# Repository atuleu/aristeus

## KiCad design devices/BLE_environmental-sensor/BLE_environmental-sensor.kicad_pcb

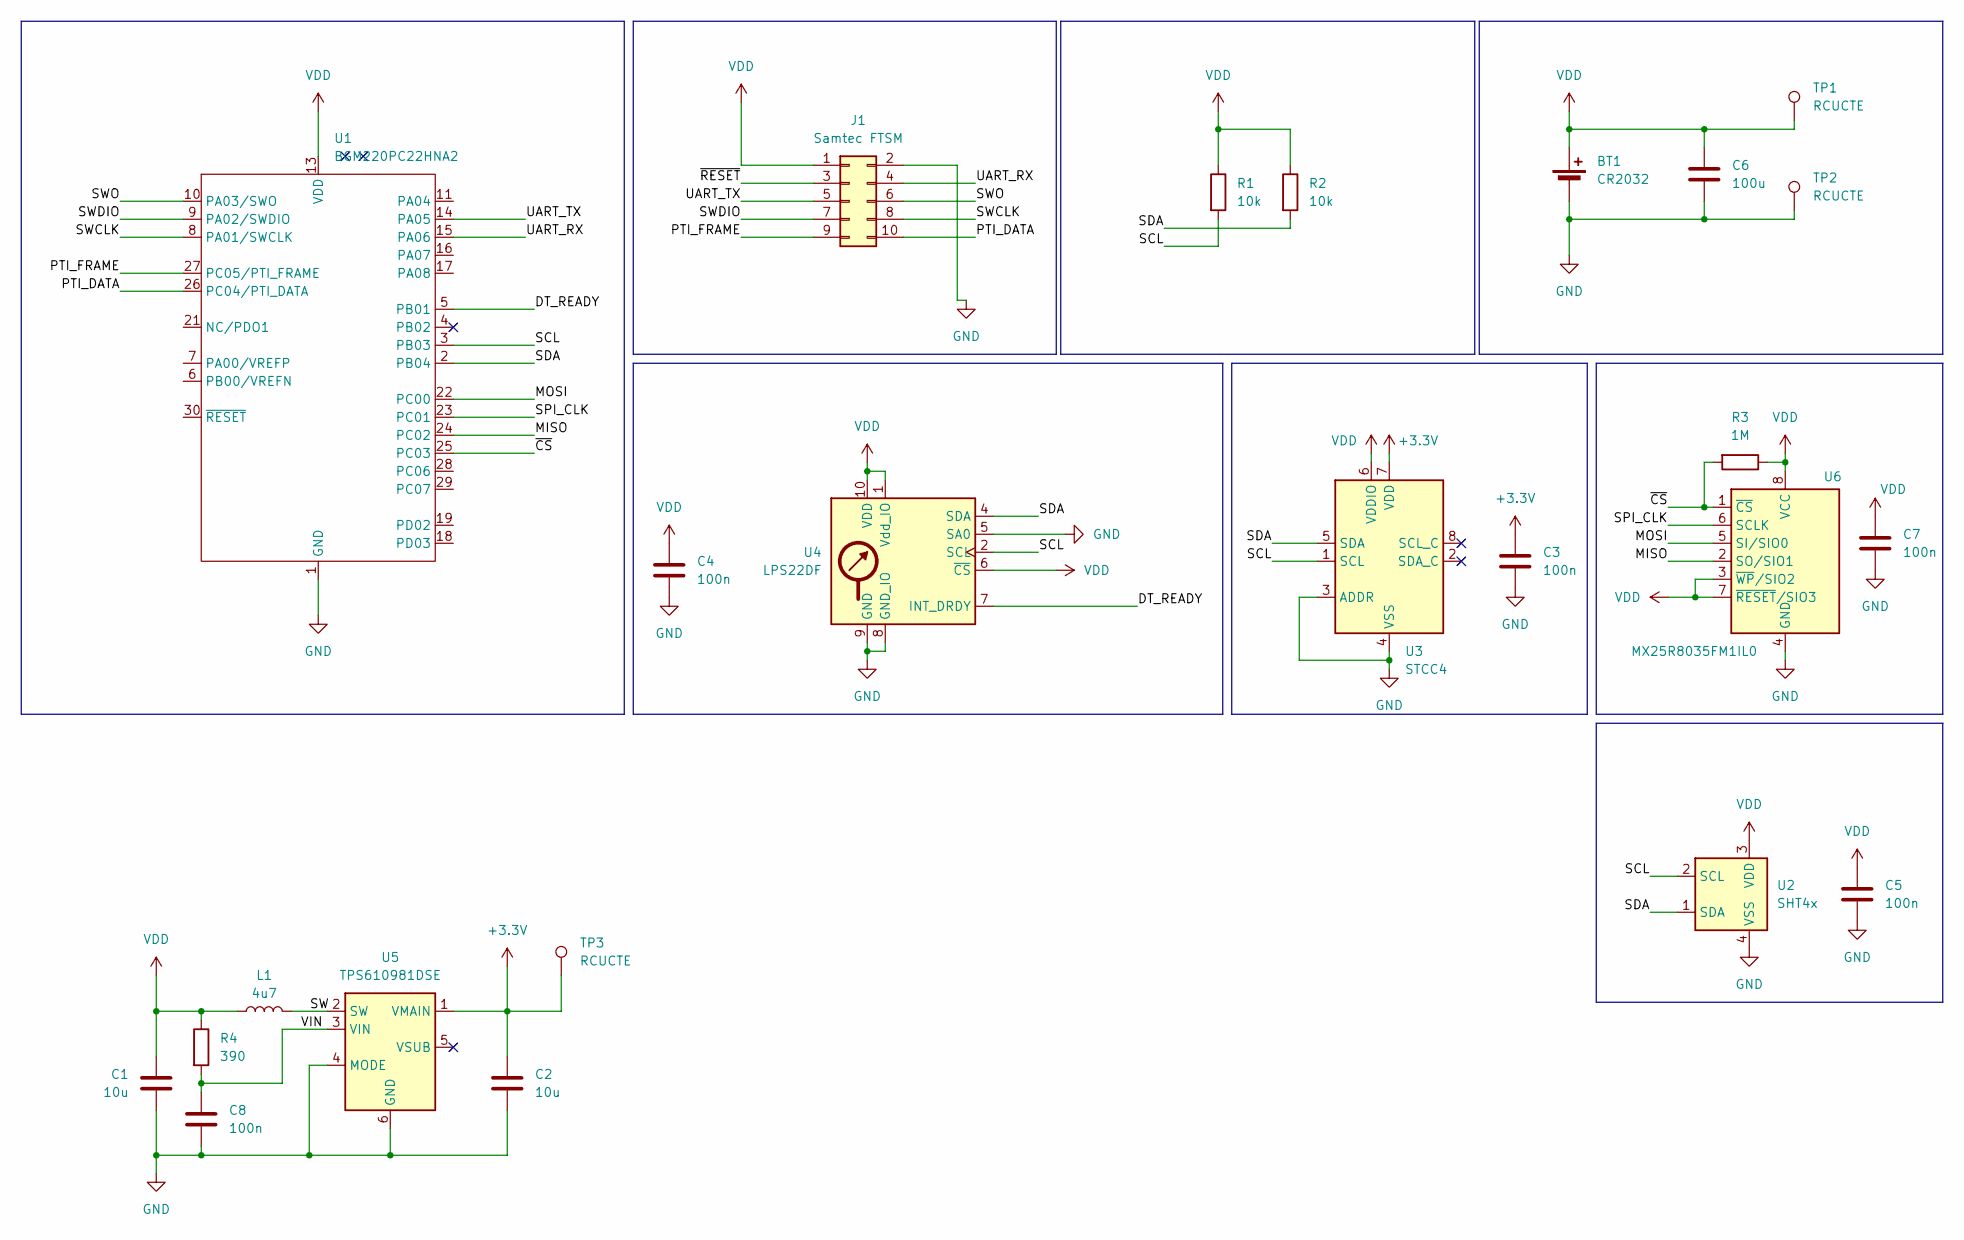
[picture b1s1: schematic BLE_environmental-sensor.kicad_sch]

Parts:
BT1: CR2032; BatteryHolder_TE_BAT-HLD-001; MPN BAT-HLD-001
C1, C2: 10u; C_0805_2012Metric; MPN GRM219R61A106KE44D
C3, C4, C5, C7, C8: 100n; C_0603_1608Metric; MPN CL10B104KB8NNNC
C6: 100u; C_1206_3216Metric; MPN CL31A107MQHNNWE
J1: Samtec FTSM; Tag-Connect_TC2050-IDC-NL_2x05_P1.27mm_Vertical; MPN TC2050-IDC-NL
L1: 4u7; L_Bourns-SRN3015; MPN SRN3015TA-4R7M
R1, R2: 10k; R_0603_1608Metric; MPN RC0603FR-0710KL
R3: 1M; R_0603_1608Metric; MPN RC0603FR-071ML
R4: 390; R_0603_1608Metric; MPN RC0603FR-07390RL
TP1, TP2, TP3: RCUCTE; MPN RCUCTE
U1: BGM220PC22HNA2; SiliconLab_BGM220P; MPN BGM220PC22HNA2
U2: SHT4x; Sensirion_DFN-4_1.5x1.5mm_P0.8mm_SHT4x_NoCentralPad; MPN SHT41-AD1F-R2
U3: STCC4; Sensirion_STCC4_4x3_P1.15mm; MPN STCC4
U4: LPS22DF; ST_HLGA-10_2x2mm_P0.5mm_LayoutBorder3x2y; MPN LPS22DFTR
U5: TPS610981DSE; WSON-6_1.5x1.5mm_P0.5mm; MPN TPS610981DSE
U6: MX25R8035FM1IL0; JEITA_SOIC-8_3.9x4.9mm_P1.27mm; MPN MX25R8035FM1IL0

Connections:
+3.3V: C2.1, C3.1, TP3.1 (1_1), U3.7 (VDD), U5.1 (VMAIN)
/DT_READY: U1.5 (PB01), U4.7 (INT_DRDY)
/MISO: U1.24 (PC02), U6.2 (SO/SIO1)
/MOSI: U1.22 (PC00), U6.5 (SI/SIO0)
/PTI_DATA: J1.10, U1.26 (PC04/PTI_DATA)
/PTI_FRAME: J1.9, U1.27 (PC05/PTI_FRAME)
/SCL: R1.2, U1.3 (PB03), U2.2 (SCL), U3.1 (SCL), U4.2 (SCL)
/SDA: R2.2, U1.2 (PB04), U2.1 (SDA), U3.5 (SDA), U4.4 (SDA)
/SPI_CLK: U1.23 (PC01), U6.6 (SCLK)
/SW: L1.2, U5.2 (SW)
/SWCLK: J1.8, U1.8 (PA01/SWCLK)
/SWDIO: J1.7, U1.9 (PA02/SWDIO)
/SWO: J1.6, U1.10 (PA03/SWO)
/UART_RX: J1.4, U1.15 (PA06)
/UART_TX: J1.5, U1.14 (PA05)
/VIN: C8.1, R4.2, U5.3 (VIN)
/~CS: R3.2, U1.25 (PC03), U6.1 (~CS)
/~RESET: J1.3
GND: BT1.2 (-), C1.2, C2.2, C3.2, C4.2, C5.2, C6.2, C7.2, C8.2, J1.2, TP2.1 (1_1), U1.1 (GND), U1.12 (GND), U1.20 (GND), U1.31 (GND), U2.4 (VSS), U3.3 (ADDR), U3.4 (VSS), U4.3 (GND), U4.5 (SA0), U4.8 (GND_IO), U4.9 (GND), U5.4 (MODE), U5.6 (GND), U6.4 (GND)
VDD: BT1.1 (+), C1.1, C4.1, C5.1, C6.1, C7.1, J1.1, L1.1, R1.1, R2.1, R3.1, R4.1, TP1.1 (1_1), U1.13 (VDD), U2.3 (VDD), U3.6 (VDDIO), U4.1 (Vdd_IO), U4.6 (~CS), U4.10 (VDD), U6.3 (~WP/SIO2), U6.7 (~RESET/SIO3), U6.8 (VCC)

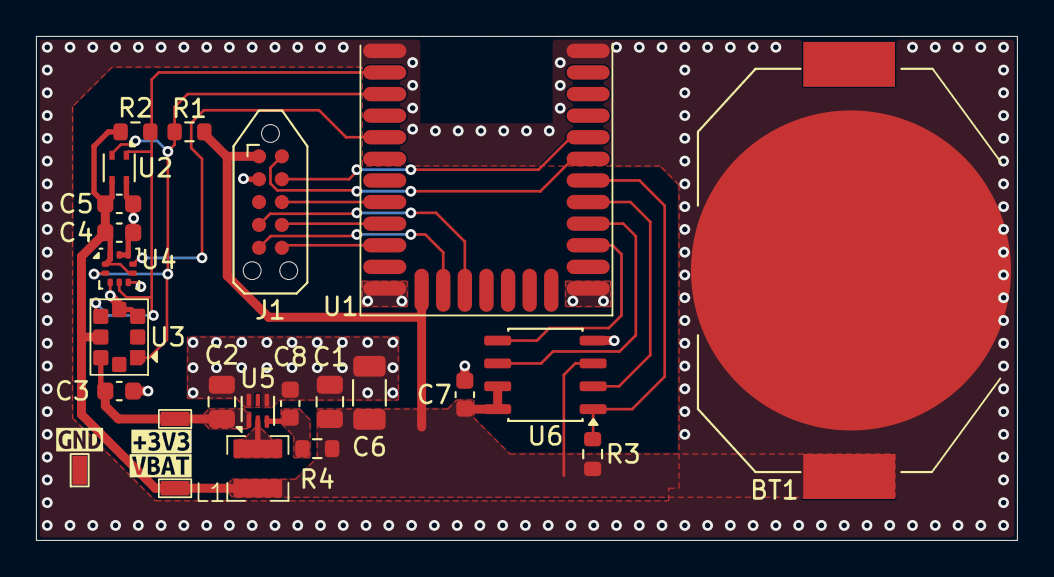
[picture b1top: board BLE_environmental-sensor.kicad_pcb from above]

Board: 2 copper layers, 54.5 x 28.0 mm, 29 parts (2 on the bottom side), 19 nets.

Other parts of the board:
kibuzzard-6A3D4B4B: G***; kibuzzard-6A3D4B4B
kibuzzard-6A3D4B8C: G***; kibuzzard-6A3D4B8C
kibuzzard-6A3D4B61: G***; kibuzzard-6A3D4B61
kibuzzard-6A3D4E4D: G***; kibuzzard-6A3D4E4D
kibuzzard-6A7308BE: G***; kibuzzard-6A7308BE

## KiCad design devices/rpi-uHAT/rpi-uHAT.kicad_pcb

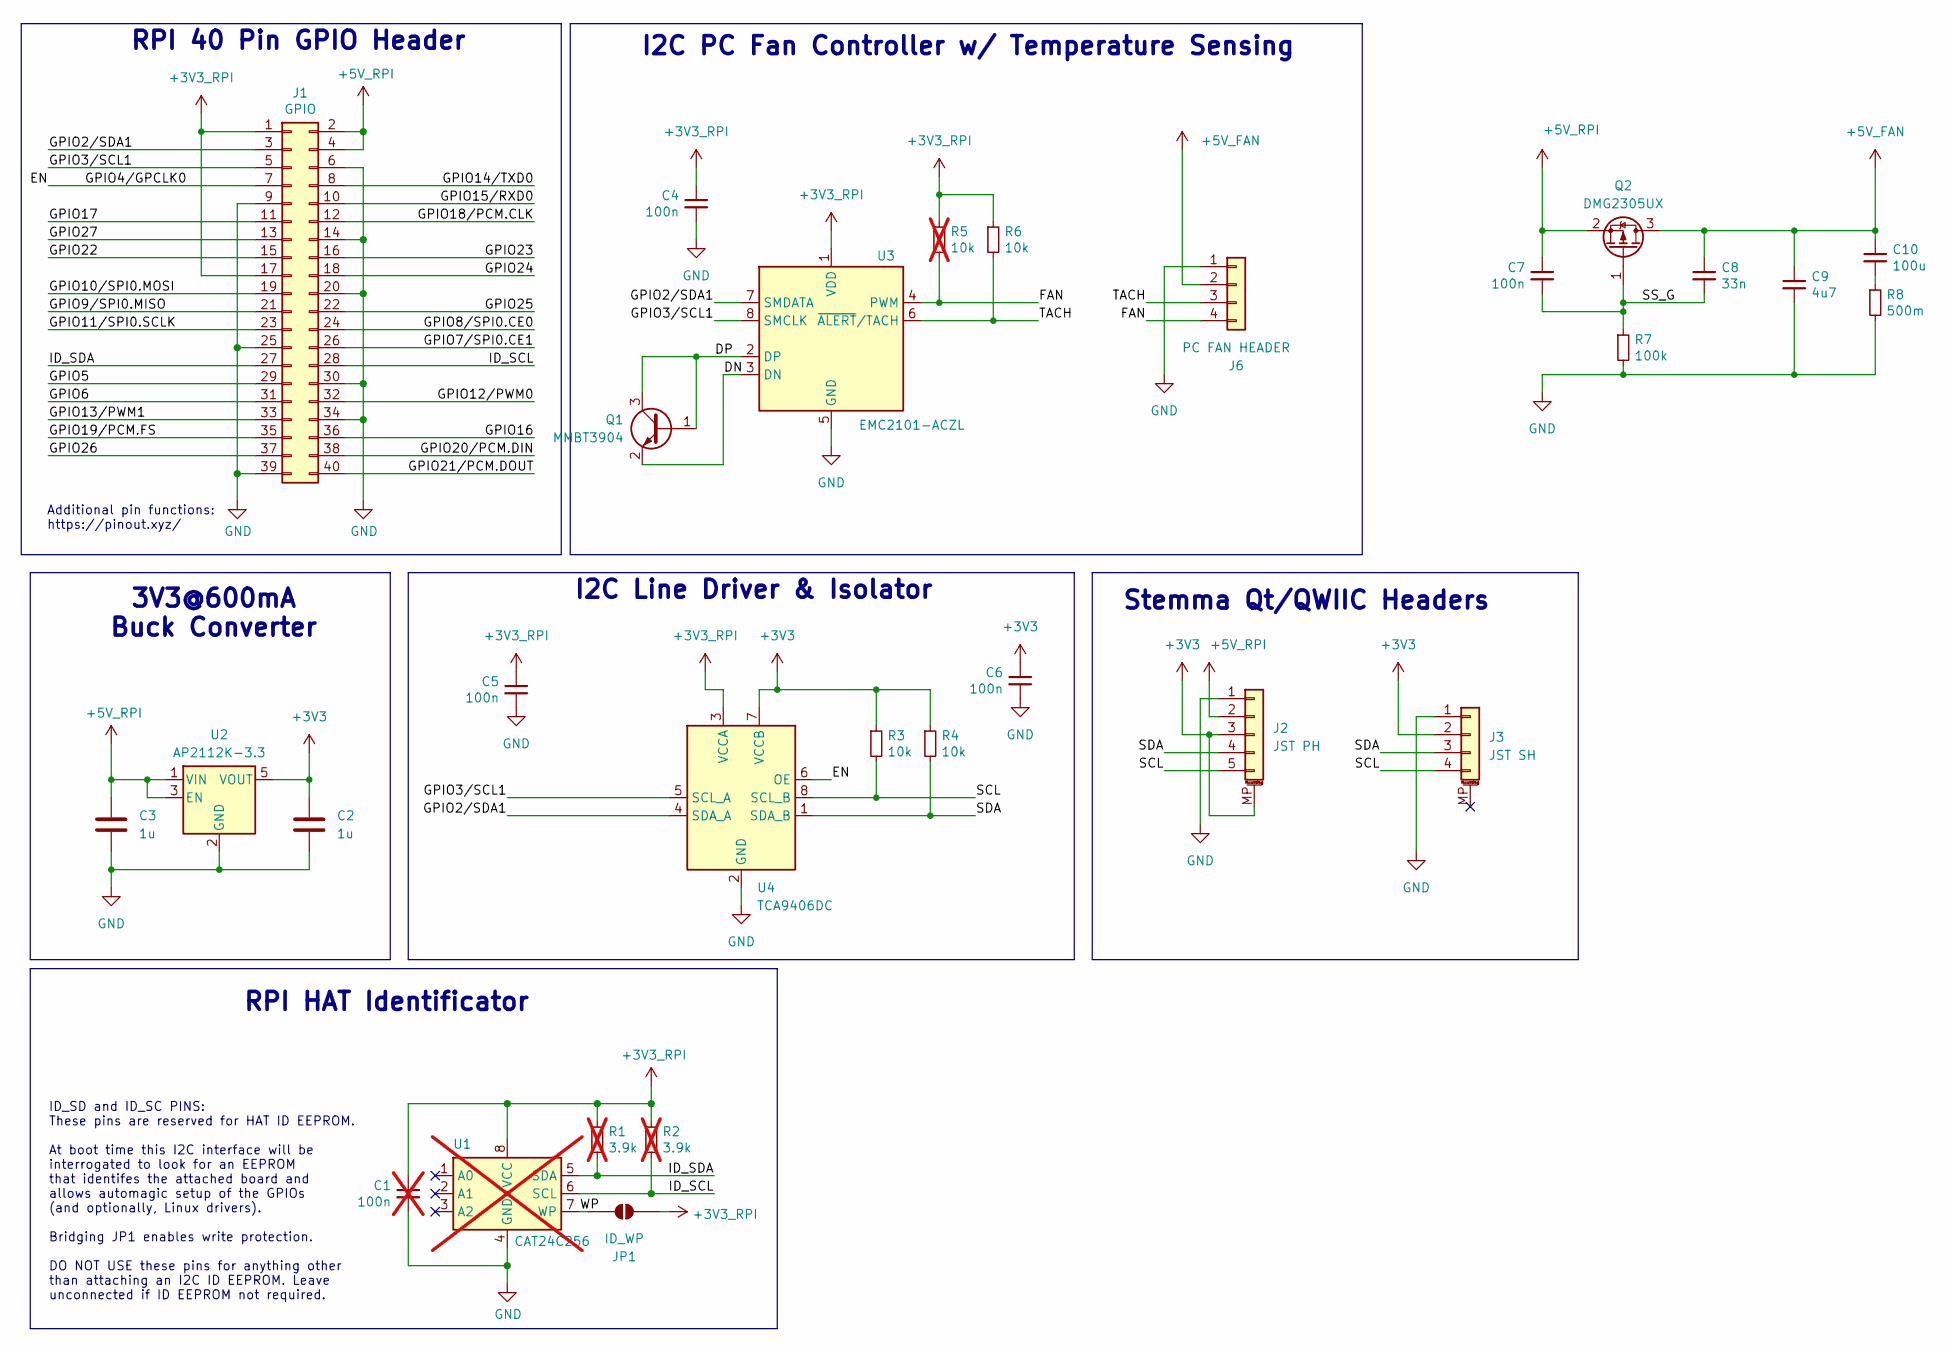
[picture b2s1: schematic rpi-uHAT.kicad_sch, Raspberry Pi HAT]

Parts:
C1: 100n; C_0603_1608Metric; MPN CL10B104KB8NNWC; not fitted
C2, C3: 1u; C_0805_2012Metric; MPN CL21B105KAFNNNE
C4, C5, C6, C7: 100n; C_0603_1608Metric; MPN CL10B104KB8NNWC
C8: 33n; C_0603_1608Metric; MPN CL10B104KB8NNWC
C9: 4u7; C_0805_2012Metric; MPN CL10B104KB8NNWC
C10: 100u; C_1206_3216Metric; MPN CL10B104KB8NNWC
J1: GPIO; PinSocket_2x20_P2.54mm_Vertical; MPN HLE-120-02-F-DV-BE
J2: JST PH; JST_PH_B5B-PH-SM4-TB_1x05-1MP_P2.00mm_Vertical; MPN B5B-PH-SM4-TB
J3: JST SH; JST_SH_BM04B-SRSS-TB_1x04-1MP_P1.00mm_Vertical; MPN BM04B-SRSS-TB
J6: PC FAN HEADER; FanPinHeader_1x04_P2.54mm_Vertical; MPN 47053-1000
JP1: ID_WP; SolderJumper-2_P1.3mm_Open_RoundedPad1.0x1.5mm
Q1: MMBT3904; SOT-23; MPN MMBT3904
Q2: DMG2305UX; SOT-23; MPN DMG2305UX
R1, R2: 3.9k; R_0603_1608Metric; MPN RC0603FR-073K9L; not fitted
R3, R4, R6: 10k; R_0603_1608Metric; MPN RC0603FR-0710KL
R5: 10k; R_0603_1608Metric; MPN RC0603FR-0710KL; not fitted
R7: 100k; R_0603_1608Metric; MPN RC0603FR-0710KL
R8: 500m; R_0603_1608Metric; MPN RC0603FR-0710KL
U1: CAT24C256; SOIC-8_3.9x4.9mm_P1.27mm; MPN CAT24C256; not fitted
U2: AP2112K-3.3; SOT-23-5; MPN AP2112K-3.3
U3: EMC2101-ACZL; MSOP-8_3x3mm_P0.65mm; MPN EMC2101-ACZL-TR
U4: TCA9406DC; TSSOP-8_3x3mm_P0.65mm; MPN TCA9406DC

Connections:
+3V3: C2.1, C6.1, J2.3, J2.MP (MountPin), J3.2, R3.1, R4.1, U2.5 (VOUT), U4.7 (VCCB)
+3V3_RPI: C1.1, C4.1, C5.1, J1.1, J1.17, JP1.2 (B), R1.1, R2.1, R5.1, R6.1, U1.8 (VCC), U3.1 (VDD), U4.3 (VCCA)
+5V_FAN: C8.1, C9.1, C10.1, J6.2, Q2.3 (D)
+5V_RPI: C3.1, C7.1, J1.2, J1.4, J2.2, Q2.2 (S), U2.1 (VIN), U2.3 (EN)
/DN: Q1.2 (E), U3.3 (DN)
/DP: Q1.1 (B), Q1.3 (C), U3.2 (DP)
/EN: J1.7, U4.6 (OE)
/FAN: J6.4, R5.2, U3.4 (PWM)
/GPIO2/SDA1: J1.3, U3.7 (SMDATA), U4.4 (SDA_A)
/GPIO3/SCL1: J1.5, U3.8 (SMCLK), U4.5 (SCL_A)
/GPIO5: J1.29
/GPIO6: J1.31
/GPIO7/SPI0.CE1: J1.26
/GPIO8/SPI0.CE0: J1.24
/GPIO9/SPI0.MISO: J1.21
/GPIO10/SPI0.MOSI: J1.19
/GPIO11/SPI0.SCLK: J1.23
/GPIO12/PWM0: J1.32
/GPIO13/PWM1: J1.33
/GPIO14/TXD0: J1.8
/GPIO15/RXD0: J1.10
/GPIO16: J1.36
/GPIO17: J1.11
/GPIO18/PCM.CLK: J1.12
/GPIO19/PCM.FS: J1.35
/GPIO20/PCM.DIN: J1.38
/GPIO21/PCM.DOUT: J1.40
/GPIO22: J1.15
/GPIO23: J1.16
/GPIO24: J1.18
/GPIO25: J1.22
/GPIO26: J1.37
/GPIO27: J1.13
/ID_SCL: J1.28, R2.2, U1.6 (SCL)
/ID_SDA: J1.27, R1.2, U1.5 (SDA)
/SCL: J2.5, J3.4, R3.2, U4.8 (SCL_B)
/SDA: J2.4, J3.3, R4.2, U4.1 (SDA_B)
/SS_G: C7.2, C8.2, Q2.1 (G), R7.1
/TACH: J6.3, R6.2, U3.6 (~ALERT/TACH)
/WP: JP1.1 (A), U1.7 (WP)
GND: C1.2, C2.2, C3.2, C4.2, C5.2, C6.2, C9.2, J1.6, J1.9, J1.14, J1.20, J1.25, J1.30, J1.34, J1.39, J2.1, J3.1, J6.1, R7.2, R8.2, U1.4 (GND), U2.2 (GND), U3.5 (GND), U4.2 (GND)
unnamed: C10.2, R8.1

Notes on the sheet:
3V3@600mA Buck Converter
I2C Line Driver & Isolator
ID_SD and ID_SC PINS: These pins are reserved for HAT ID EEPROM. At boot time this I2C interface will be interrogated to look for an EEPROM that identifes the attached board and allows automagic setup of the GPIOs (and optionally, Linux drivers). Bridging JP1 enables write protection. DO NOT USE th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
RPI 40 Pin GPIO Header
Stemma Qt/QWIIC Headers
I2C PC Fan Controller w/ Temperature Sensing
RPI HAT Identificator
Additional pin functions: https://pinout.xyz/

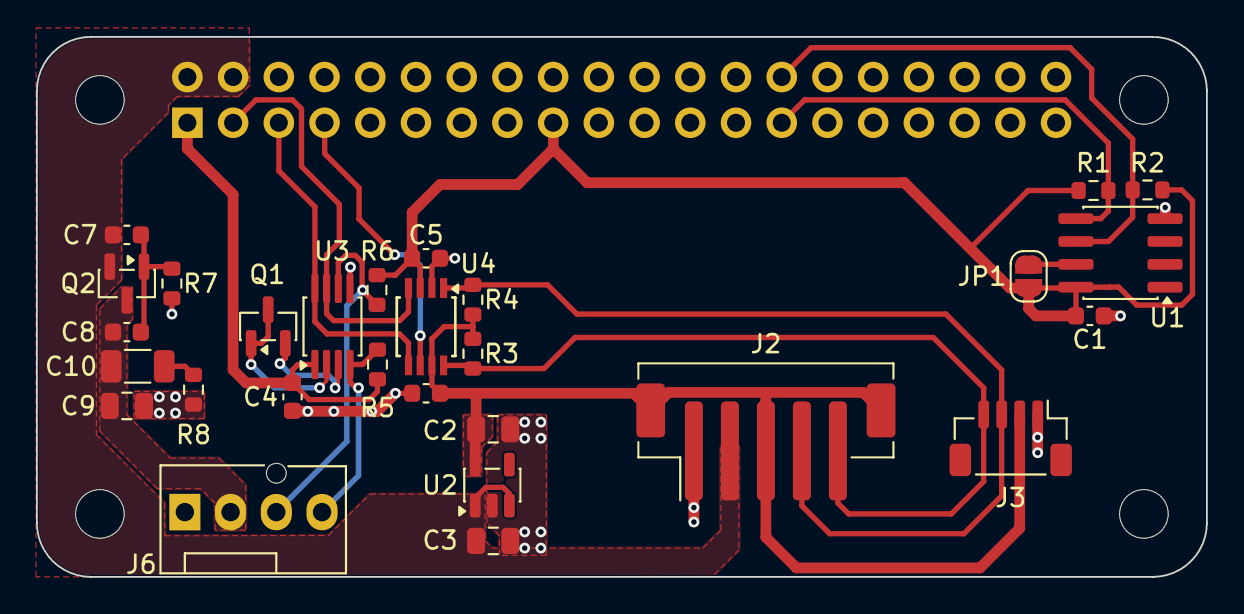
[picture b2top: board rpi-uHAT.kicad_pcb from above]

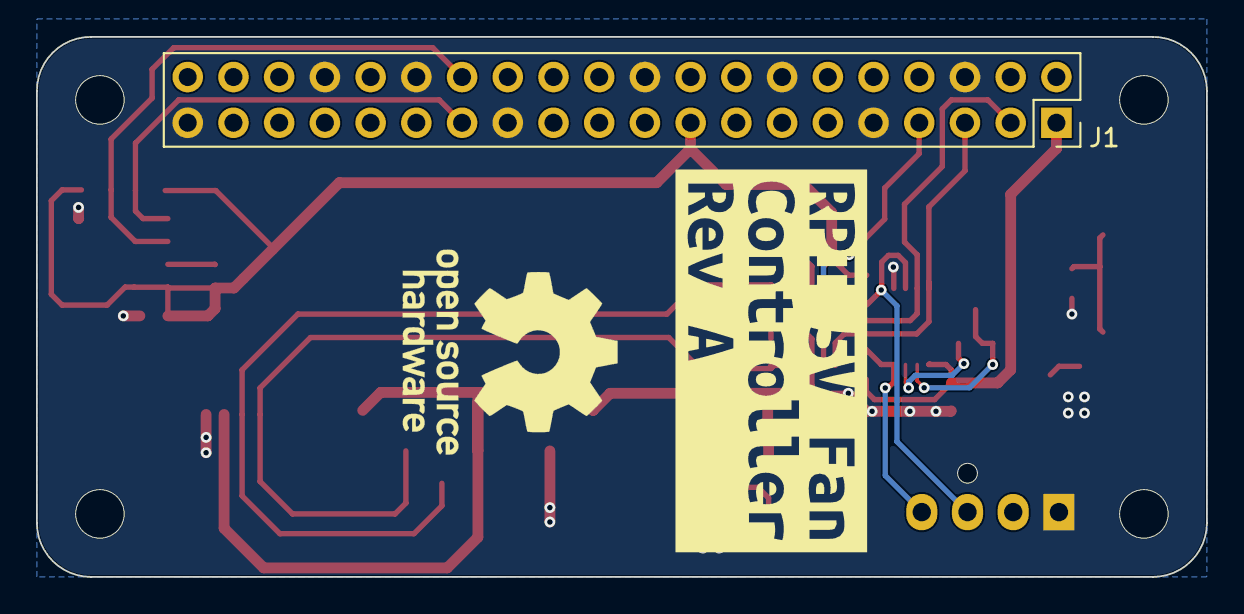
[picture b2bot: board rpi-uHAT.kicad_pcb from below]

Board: 2 copper layers, 65.0 x 30.0 mm, 34 parts (2 on the bottom side), 19 nets.

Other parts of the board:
MH1, MH2, MH3, MH4: MountingHole_2.7mm_M2.5
kibuzzard-6A731D1D: G***; kibuzzard-6A731D1D

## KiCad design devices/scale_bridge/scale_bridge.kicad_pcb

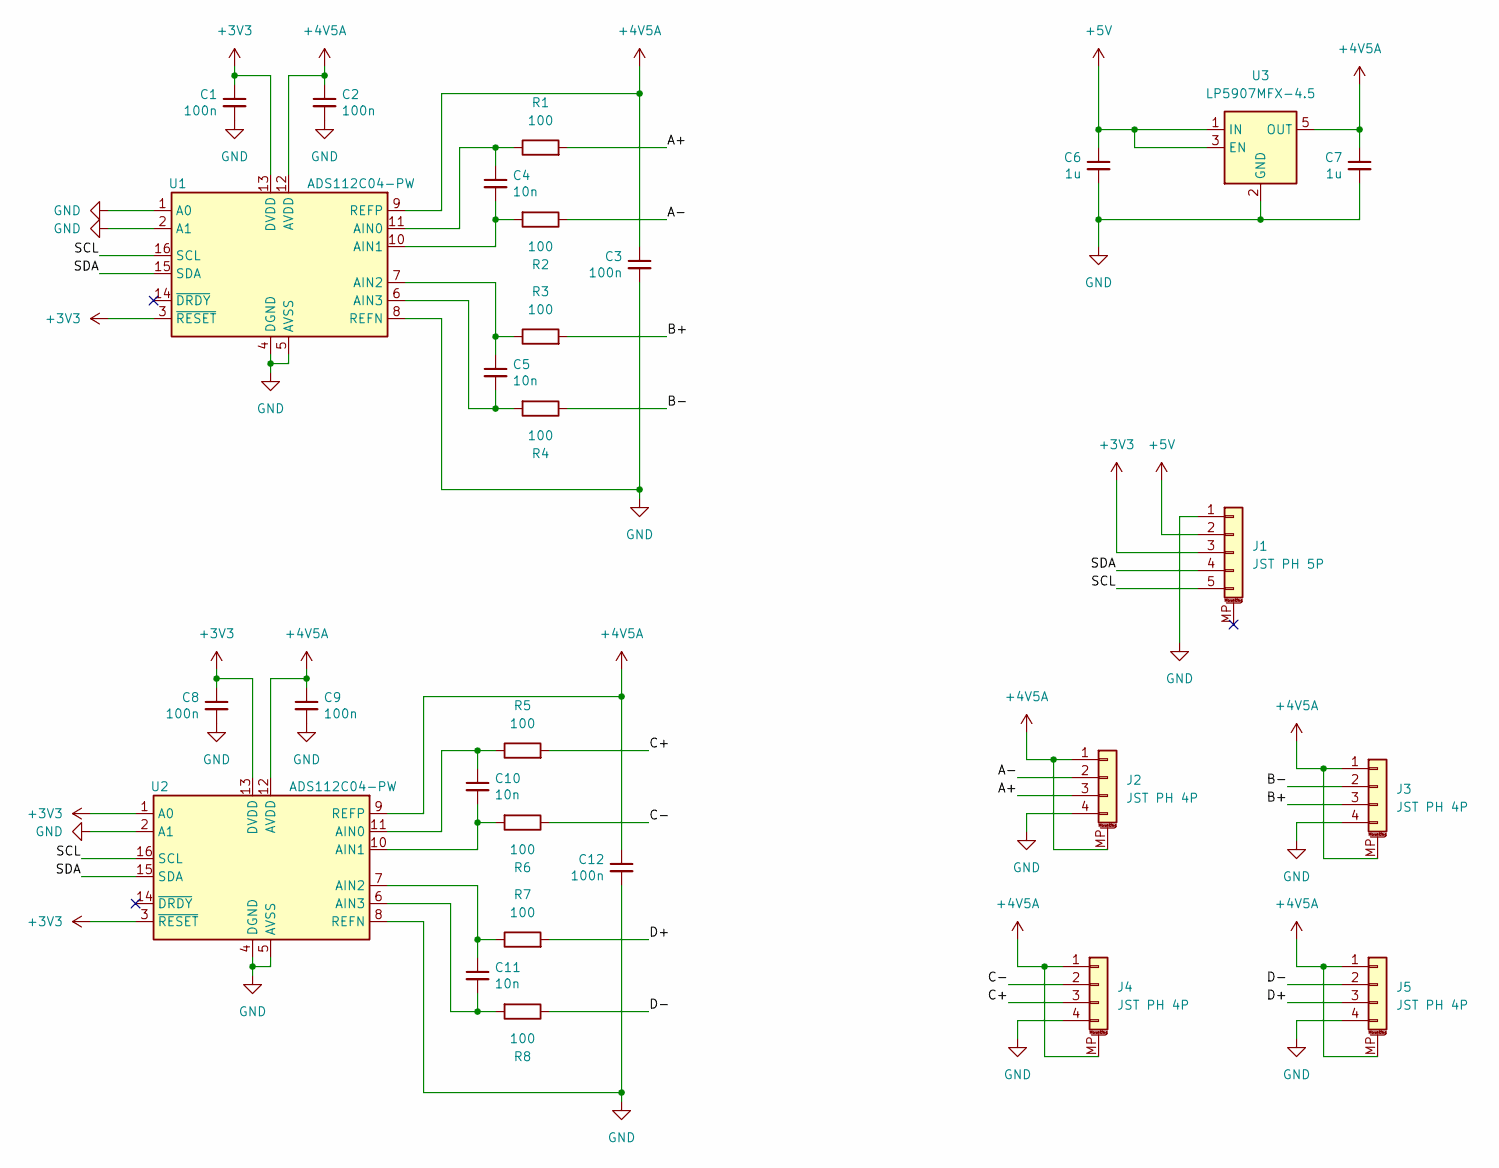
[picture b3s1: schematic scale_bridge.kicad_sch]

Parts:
C1, C2, C8, C9: 100n; C_0603_1608Metric; MPN CL10B104KB8NNWC
C3, C12: 100n; C_1206_3216Metric; MPN GRM3195C1H104JA05D
C4, C5, C10, C11: 10n; C_0603_1608Metric; MPN GRM1885C1H103JA01D
C6, C7: 1u; C_0603_1608Metric; MPN CL10B105KA8NNNC
J1: JST PH 5P; JST_PH_S5B-PH-SM4-TB_1x05-1MP_P2.00mm_Horizontal
J2, J3, J4, J5: JST PH 4P; JST_PH_S4B-PH-SM4-TB_1x04-1MP_P2.00mm_Horizontal
R1, R2, R3, R4, R5, R6, R7, R8: 100; R_0603_1608Metric
U1, U2: ADS112C04-PW; TSSOP-16_4.4x5mm_P0.65mm
U3: LP5907MFX-4.5; SOT-23-5

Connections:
+3V3: C1.1, C8.1, J1.3, U1.3 (~RESET), U1.13 (DVDD), U2.1 (A0), U2.3 (~RESET), U2.13 (DVDD)
+4V5A: C2.1, C3.1, C7.1, C9.1, C12.1, J2.1, J2.MP (MountPin), J3.1, J3.MP (MountPin), J4.1, J4.MP (MountPin), J5.1, J5.MP (MountPin), U1.9 (REFP), U1.12 (AVDD), U2.9 (REFP), U2.12 (AVDD), U3.5 (OUT)
+5V: C6.1, J1.2, U3.1 (IN), U3.3 (EN)
/A+: J2.3, R1.2
/A-: J2.2, R2.1
/B+: J3.3, R3.2
/B-: J3.2, R4.1
/C+: J4.3, R5.2
/C-: J4.2, R6.1
/D+: J5.3, R7.2
/D-: J5.2, R8.1
/SCL: J1.5, U1.16 (SCL), U2.16 (SCL)
/SDA: J1.4, U1.15 (SDA), U2.15 (SDA)
GND: C1.2, C2.2, C3.2, C6.2, C7.2, C8.2, C9.2, C12.2, J1.1, J2.4, J3.4, J4.4, J5.4, U1.1 (A0), U1.2 (A1), U1.4 (DGND), U1.5 (AVSS), U1.8 (REFN), U2.2 (A1), U2.4 (DGND), U2.5 (AVSS), U2.8 (REFN), U3.2 (GND)
unnamed: C4.1, R1.1, U1.11 (AIN0)
unnamed: C4.2, R2.2, U1.10 (AIN1)
unnamed: C5.1, R3.1, U1.7 (AIN2)
unnamed: C5.2, R4.2, U1.6 (AIN3)
unnamed: C10.1, R5.1, U2.11 (AIN0)
unnamed: C10.2, R6.2, U2.10 (AIN1)
unnamed: C11.1, R7.1, U2.7 (AIN2)
unnamed: C11.2, R8.2, U2.6 (AIN3)

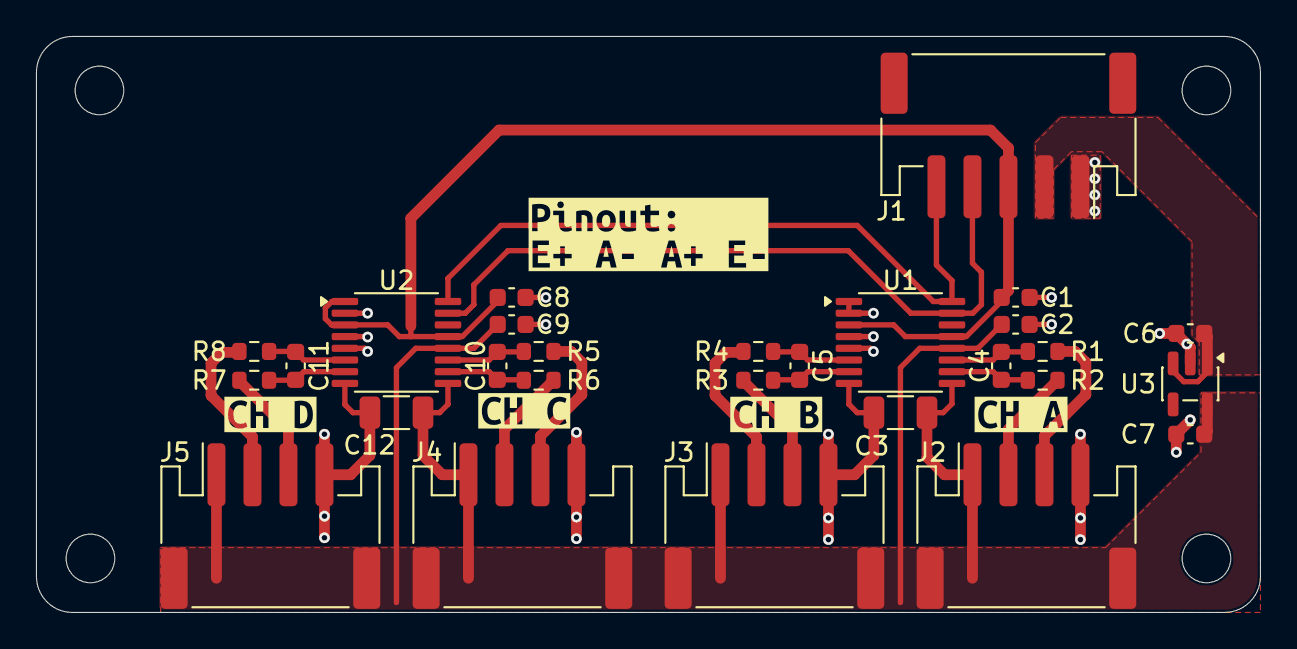
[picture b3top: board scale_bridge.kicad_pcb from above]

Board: 2 copper layers, 68.0 x 32.0 mm, 33 parts (0 on the bottom side), 22 nets.

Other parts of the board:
kibuzzard-6A2812B5: G***; kibuzzard-6A2812B5
kibuzzard-6A28120C: G***; kibuzzard-6A28120C
kibuzzard-6A28126F: G***; kibuzzard-6A28126F
kibuzzard-6A281260: G***; kibuzzard-6A281260
kibuzzard-6A281267: G***; kibuzzard-6A281267

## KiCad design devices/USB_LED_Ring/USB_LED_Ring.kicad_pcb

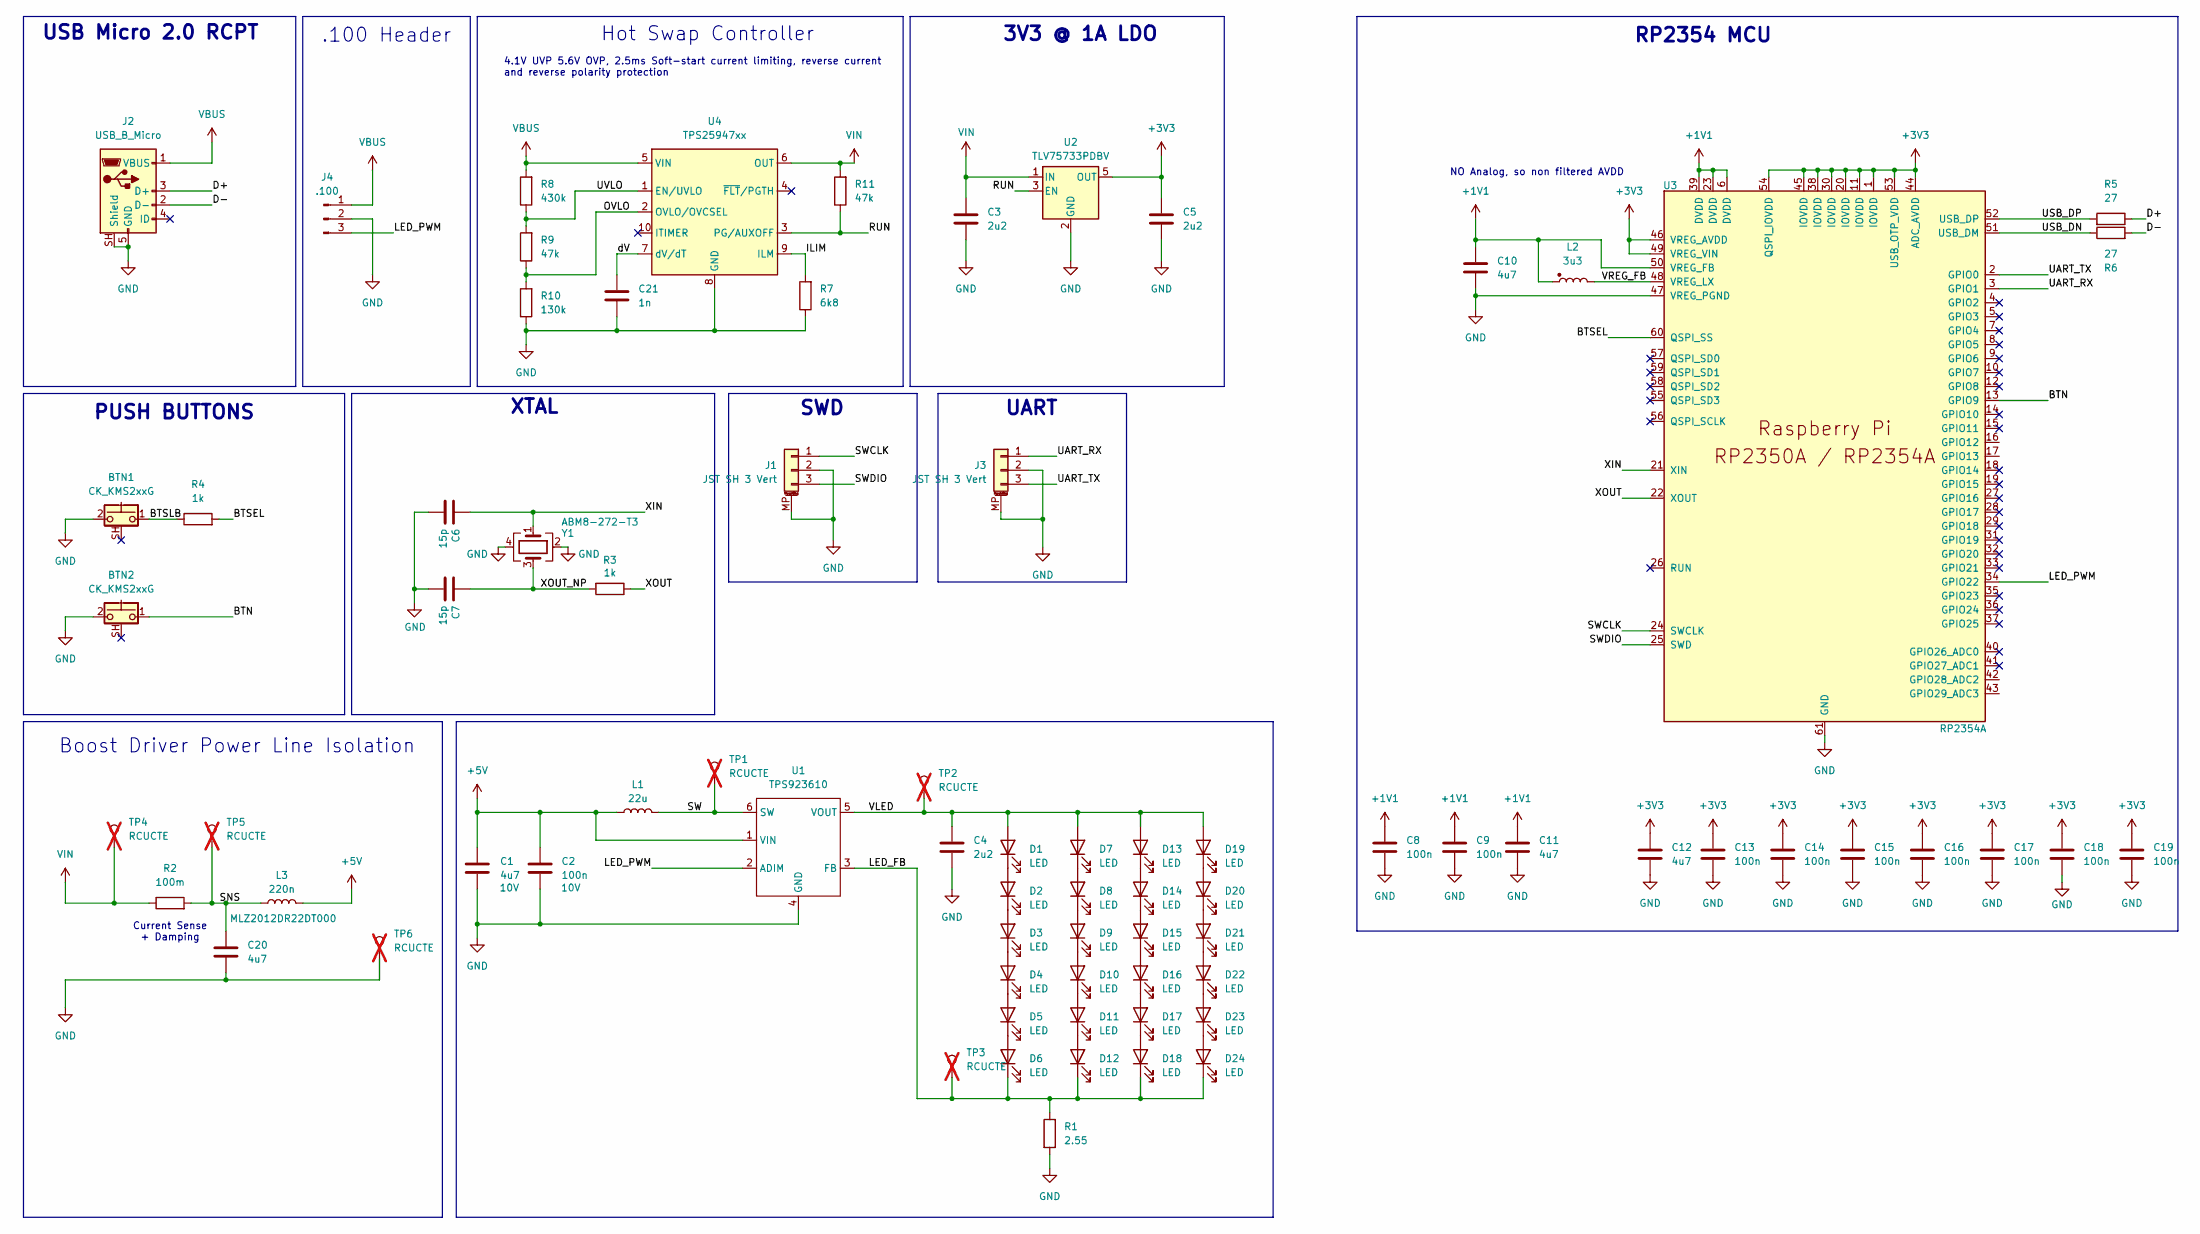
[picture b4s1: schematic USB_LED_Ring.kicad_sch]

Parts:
BTN1, BTN2: CK_KMS2xxG; SW_SPST_CK_KMS2xxGP; MPN KMS231GP LFS
C1: 4u7; C_0805_2012Metric; Voltage Rating 10V; MPN GRM21BZ71H475ME15
C2: 100n; C_0402_1005Metric; Voltage Rating 10V; MPN CL05B104KO5NNN
C3, C4, C5: 2u2; C_0805_2012Metric; MPN CL21B225KBYNNWE
C6, C7: 15p; C_0402_1005Metric; MPN GCM1555C1H150JA16D
C8, C9, C13, C14, C15, C16, C17, C18, C19: 100n; C_0402_1005Metric; MPN CL05B104KO5NNN
C10, C11, C12: 4u7; C_0603_1608Metric; MPN GRM188Z71A475ME15D
C20: 4u7; C_0805_2012Metric; MPN GRM21BZ71H475ME15
C21: 1n; C_0402_1005Metric; MPN GRM1555C1H102JA01D
D1, D2, D3, D4, D5, D6, D7, D8, D9, D10, D11, D12, D13, D14, D15, D16, D17, D18, D19, D20, D21, D22, D23, D24: LED; 158301250; MPN 158301250
J1, J3: JST SH 3 Vert; JST_SH_BM03B-SRSS-TB_1x03-1MP_P1.00mm_Vertical; MPN BM03B-SRSS-TB
J2: USB_B_Micro; USB_Micro-B_Molex-105017-0001; MPN 105017-0001
J4: .100; PinHeader_1x03_P2.54mm_Vertical
L1: 22u; L_Bourns-SRN3015; MPN LQH3NPN220MMEL
L2: 3u3; L_Abracon_AOTA; MPN AOTA-B252010S3R3MT
L3: 220n; LED_0805_2012Metric; MPN MLZ2012DR22DT000
R1: 2.55; R_0603_1608Metric; MPN CPF0603B2R55E1
R2: 100m; R_0603_1608Metric; MPN KDV06FR100ET
R3, R4: 1k; R_0402_1005Metric; MPN RC0402FR-071KL
R5, R6: 27; R_0402_1005Metric; MPN RC0402FR-0727RL
R7: 6k8; R_0402_1005Metric; MPN RC0402FR-076K8L
R8: 430k; R_0402_1005Metric; MPN RC0402FR-07430KL
R9, R11: 47k; R_0402_1005Metric; MPN RC0402FR-0747KL
R10: 130k; R_0402_1005Metric; MPN RC0402FR-07130KL
TP1, TP2, TP3, TP4, TP5, TP6: RCUCTE; MPN RCUCTE; not fitted
U1: TPS923610; SOT-563; MPN TPS923610DRLR
U2: TLV75733PDBV; SOT-23-5; MPN TLV75733PDBV
U3: RP2354A; RP2350-QFN-60-1EP_7x7_P0.4mm_EP3.4x3.4mm_ThermalVias; MPN RP2354A
U4: TPS25947xx; Texas_RPW_VQFN-HR-10_2.1x2.1mm_P0.475mm; MPN TPS2594720RPW
Y1: ABM8-272-T3; Crystal_SMD_3225-4Pin_3.2x2.5mm; MPN ABM8-272-T3

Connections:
+1V1: C8.1, C9.1, C10.1, C11.1, L2.1, U3.6 (DVDD), U3.23 (DVDD), U3.39 (DVDD), U3.50 (VREG_FB)
+3V3: C5.1, C12.1, C13.1, C14.1, C15.1, C16.1, C17.1, C18.1, C19.1, U2.5 (OUT), U3.1 (IOVDD), U3.11 (IOVDD), U3.20 (IOVDD), U3.30 (IOVDD), U3.38 (IOVDD), U3.44 (ADC_AVDD), U3.45 (IOVDD), U3.46 (VREG_AVDD), U3.49 (VREG_VIN), U3.53 (USB_OTP_VDD), U3.54 (QSPI_IOVDD)
+5V: C1.1, C2.1, L1.1, L3.2, U1.1 (VIN)
/BTN: BTN2.1, U3.13 (GPIO9)
/BTSEL: R4.2, U3.60 (QSPI_SS)
/BTSLB: BTN1.1, R4.1
/D+: J2.3 (D+), R5.1
/D-: J2.2 (D-), R6.2
/ILIM: R7.2, U4.9 (ILM)
/LED_FB: D6.1 (K), D12.1 (K), D18.1 (K), D24.1 (K), R1.1, TP3.1 (1_1), U1.3 (FB)
/LED_PWM: J4.3, U1.2 (ADIM), U3.34 (GPIO22)
/OVLO: R9.1, R10.2, U4.2 (OVLO/OVCSEL)
/RUN: R11.1, U2.3 (EN), U4.3 (PG/AUXOFF)
/SNS: C20.1, L3.1, R2.2, TP5.1 (1_1)
/SW: L1.2, TP1.1 (1_1), U1.6 (SW)
/SWCLK: J1.1, U3.24 (SWCLK)
/SWDIO: J1.3, U3.25 (SWD)
/UART_RX: J3.1, U3.3 (GPIO1)
/UART_TX: J3.3, U3.2 (GPIO0)
/USB_DN: R6.1, U3.51 (USB_DM)
/USB_DP: R5.2, U3.52 (USB_DP)
/UVLO: R8.1, R9.2, U4.1 (EN/UVLO)
/VLED: C4.1, D1.2 (A), D7.2 (A), D13.2 (A), D19.2 (A), TP2.1 (1_1), U1.5 (VOUT)
/VREG_FB: L2.2, U3.48 (VREG_LX)
/XIN: C6.1, U3.21 (XIN), Y1.1
/XOUT: R3.1, U3.22 (XOUT)
/XOUT_NP: C7.1, R3.2, Y1.3
/dV: C21.1, U4.7 (dV/dT)
GND: BTN1.2, BTN2.2, C1.2, C2.2, C3.2, C4.2, C5.2, C6.2, C7.2, C8.2, C9.2, C10.2, C11.2, C12.2, C13.2, C14.2, C15.2, C16.2, C17.2, C18.2, C19.2, C20.2, C21.2, J1.2, J1.MP (MountPin), J2.5 (GND), J2.SH (Shield), J3.2, J3.MP (MountPin), J4.2, R1.2, R7.1, R10.1, TP6.1 (1_1), U1.4 (GND), U2.2 (GND), U3.47 (VREG_PGND), U3.61 (GND), U4.8 (GND), Y1.2, Y1.4
unnamed: D1.1 (K), D2.2 (A)
unnamed: D2.1 (K), D3.2 (A)
unnamed: D3.1 (K), D4.2 (A)
unnamed: D4.1 (K), D5.2 (A)
unnamed: D5.1 (K), D6.2 (A)
unnamed: D7.1 (K), D8.2 (A)
unnamed: D8.1 (K), D9.2 (A)
unnamed: D9.1 (K), D10.2 (A)
unnamed: D10.1 (K), D11.2 (A)
unnamed: D11.1 (K), D12.2 (A)
unnamed: D13.1 (K), D14.2 (A)
unnamed: D14.1 (K), D15.2 (A)
unnamed: D15.1 (K), D16.2 (A)
unnamed: D16.1 (K), D17.2 (A)
unnamed: D17.1 (K), D18.2 (A)
unnamed: D19.1 (K), D20.2 (A)
unnamed: D20.1 (K), D21.2 (A)
unnamed: D21.1 (K), D22.2 (A)
unnamed: D22.1 (K), D23.2 (A)
unnamed: D23.1 (K), D24.2 (A)
VBUS: J2.1 (VBUS), J4.1, R8.2, U4.5 (VIN)
VIN: C3.1, R2.1, R11.2, TP4.1 (1_1), U2.1 (IN), U4.6 (OUT)

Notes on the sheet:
Current Sense + Damping
NO Analog, so non filtered AVDD
XTAL
USB Micro 2.0 RCPT
Hot Swap Controller
Boost Driver Power Line Isolation
UART
3V3 @ 1A LDO
.100 Header
SWD
PUSH BUTTONS
RP2354 MCU
4.1V UVP 5.6V OVP, 2.5ms Soft-start current limiting, reverse current and reverse polarity protection

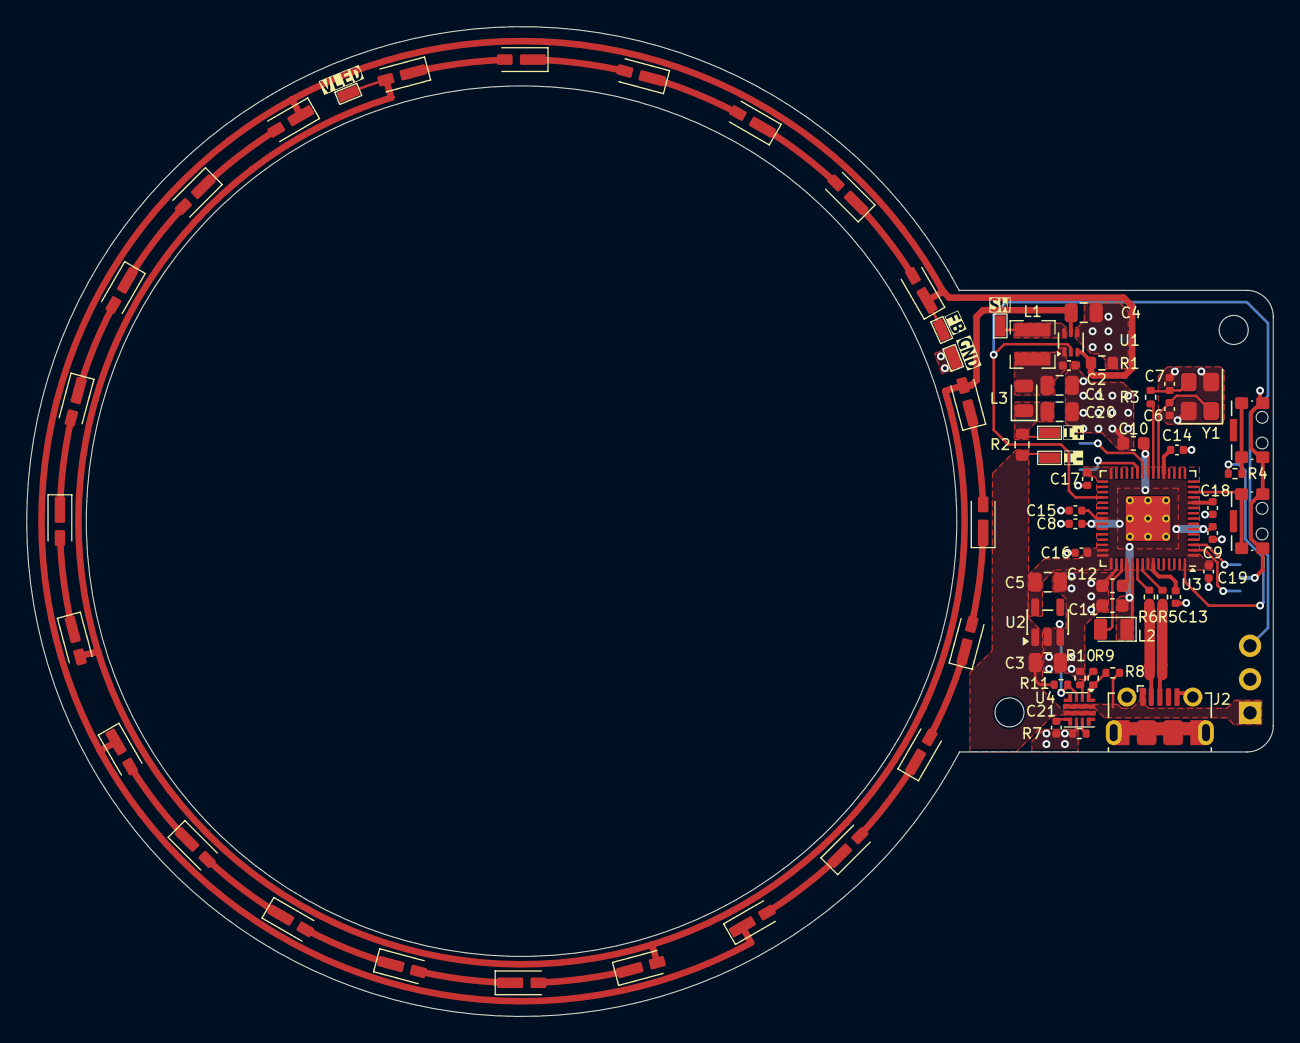
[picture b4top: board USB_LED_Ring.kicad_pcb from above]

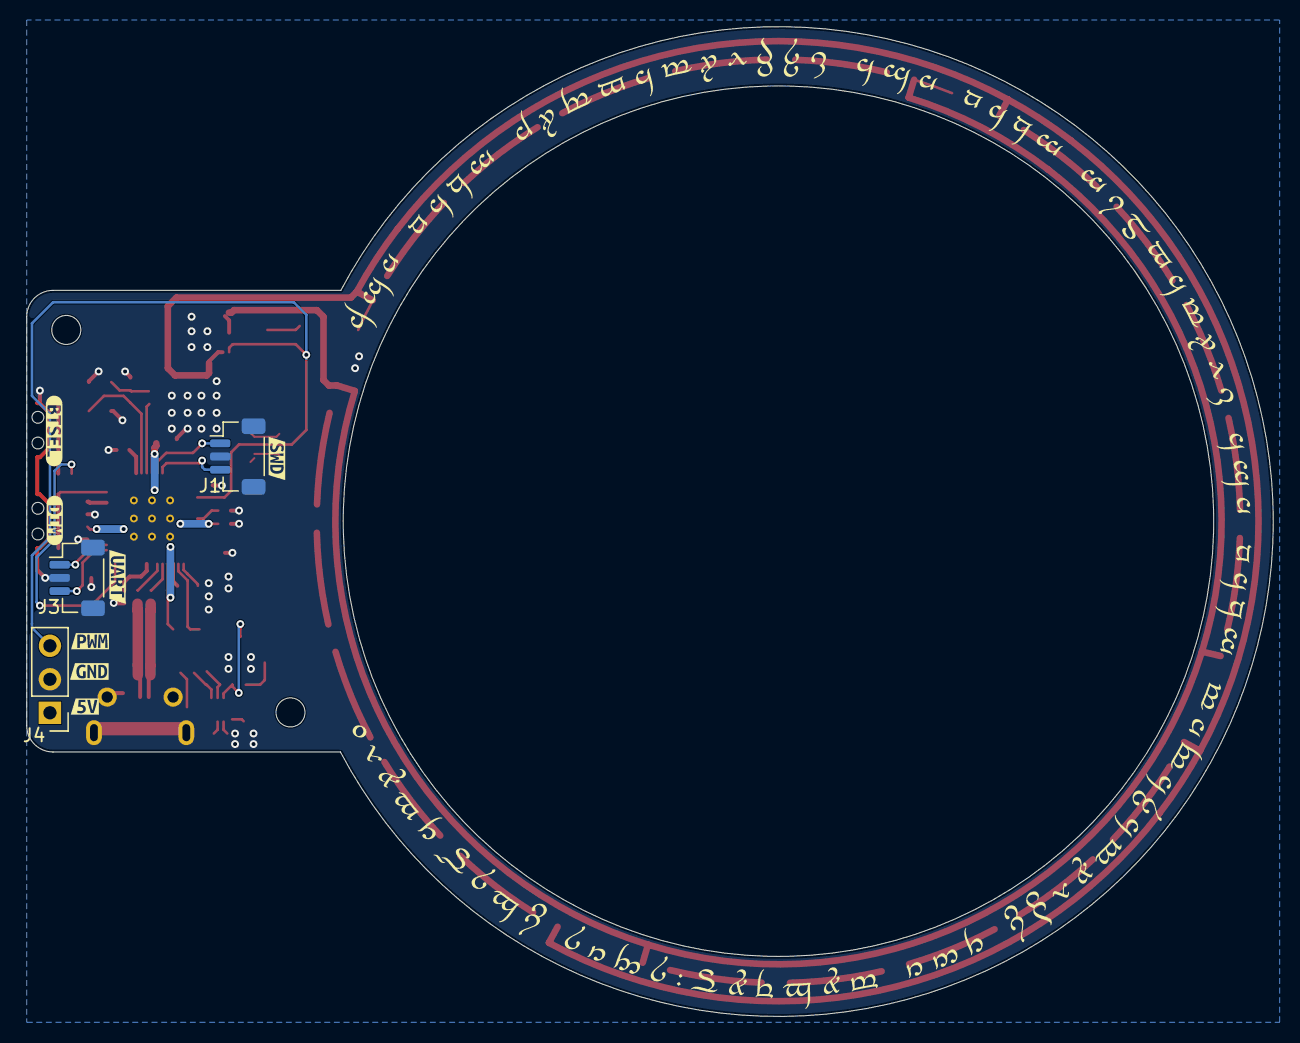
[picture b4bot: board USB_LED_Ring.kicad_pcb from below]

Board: 2 copper layers, 94.5 x 75.0 mm, 89 parts (10 on the bottom side), 51 nets.

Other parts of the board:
kibuzzard-6A15B5C8: G***; kibuzzard-6A15B5C8
kibuzzard-6A15B5E0: G***; kibuzzard-6A15B5E0
kibuzzard-6A15B6D3: G***; kibuzzard-6A15B6D3
kibuzzard-6A15B60A: G***; kibuzzard-6A15B60A
kibuzzard-6A15B584: G***; kibuzzard-6A15B584
kibuzzard-6A11723A: G***; kibuzzard-6A11723A
kibuzzard-6A117223: G***; kibuzzard-6A117223
kibuzzard-69FB677C: G***; kibuzzard-69FB677C
kibuzzard-69FB681A: G***; kibuzzard-69FB681A
kibuzzard-69FB6775: G***; kibuzzard-69FB6775
kibuzzard-69FB6788: G***; kibuzzard-69FB6788
kibuzzard-69FB6831: G***; kibuzzard-69FB6831
kibuzzard-69FC837B: G***; kibuzzard-69FC837B

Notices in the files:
devices/rpi-uHAT/rpi-uHAT.kicad_sch:
Licensed under OSHW License 2 restrictive
